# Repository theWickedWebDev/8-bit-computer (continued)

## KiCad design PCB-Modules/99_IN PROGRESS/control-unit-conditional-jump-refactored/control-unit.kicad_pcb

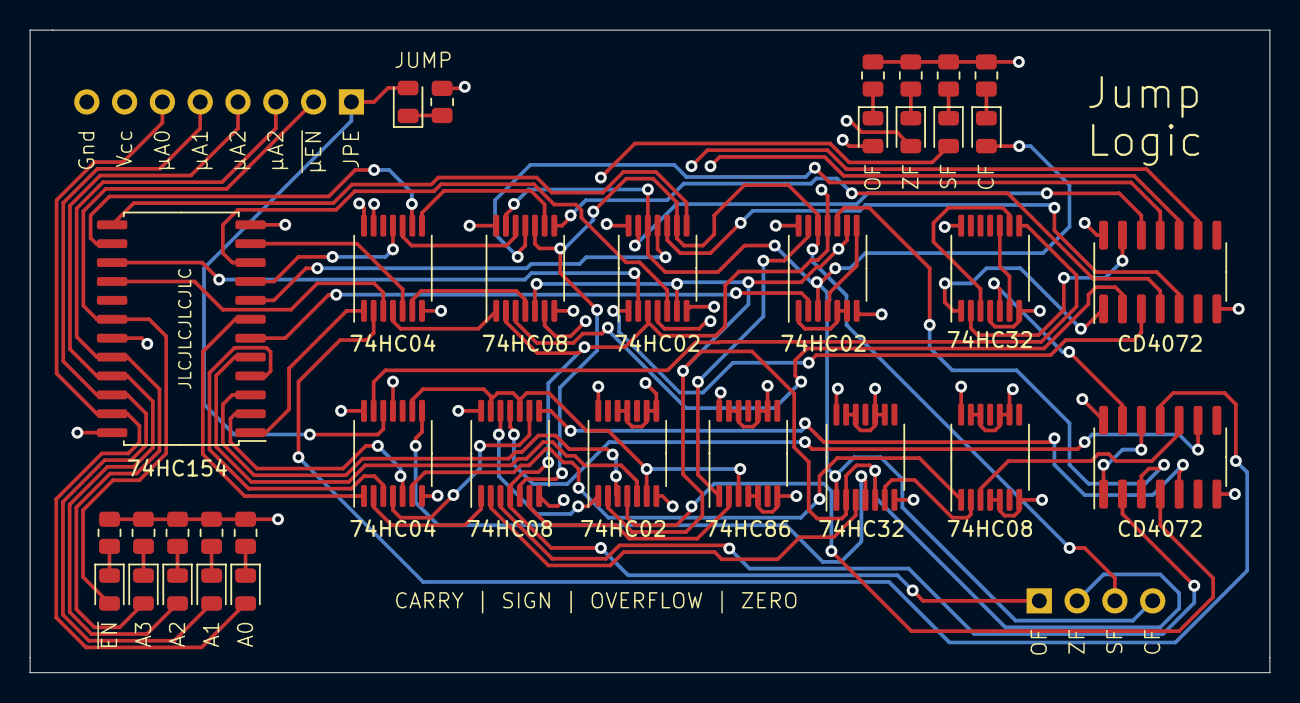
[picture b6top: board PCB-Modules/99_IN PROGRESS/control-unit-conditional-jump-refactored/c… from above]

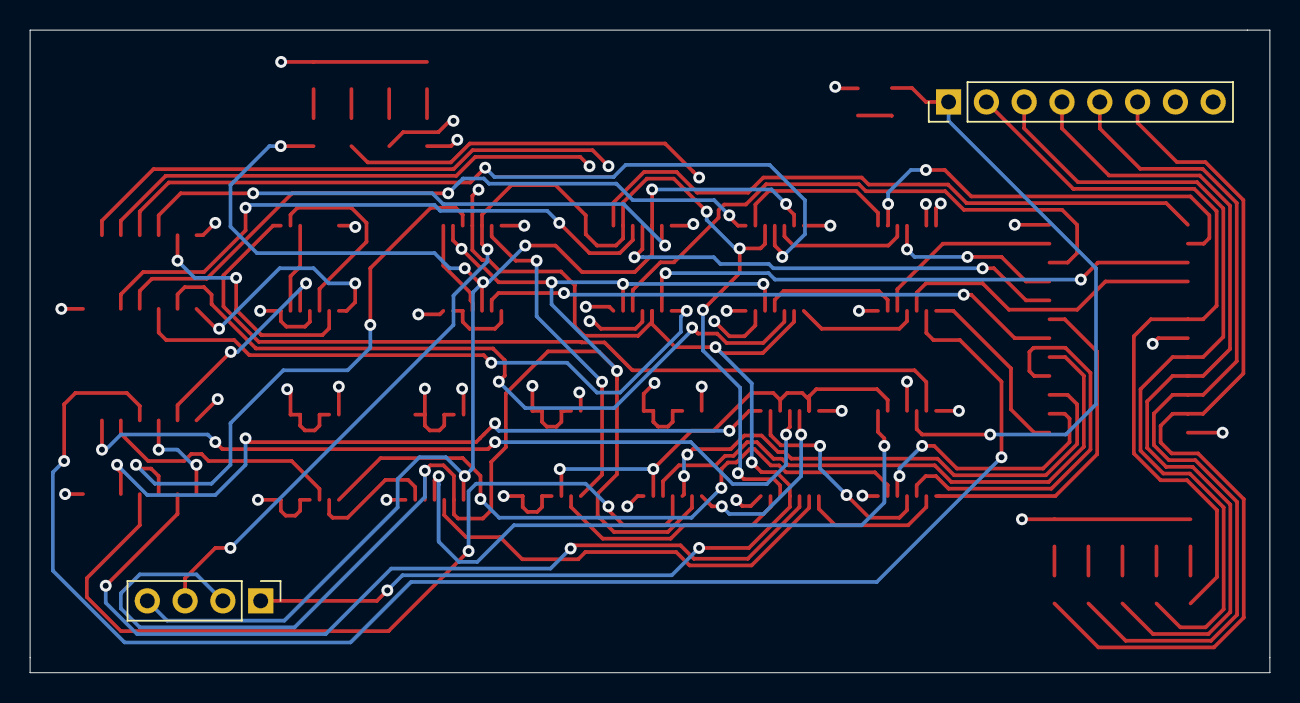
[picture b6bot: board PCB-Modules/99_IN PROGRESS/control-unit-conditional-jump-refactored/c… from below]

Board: 4 copper layers, 83.3 x 43.2 mm, 36 parts (2 on the bottom side), 75 nets.

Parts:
D1, D2, D3, D4, D5, D6, D7, D8, D9, D10: LED; LED_0805_2012Metric
J3: Conn_01x08; PinHeader_1x08_P2.54mm_Vertical
J4: Conn_01x04; PinHeader_1x04_P2.54mm_Vertical
R1, R2, R3, R4, R5, R6, R7, R8, R9, R10: R_US; R_0805_2012Metric
U1, U4: 74LS04; TSSOP-14_4.4x5mm_P0.65mm
U2, U5, U9: 74LS02; TSSOP-14_4.4x5mm_P0.65mm
U3, U6, U14: 74LS08; TSSOP-14_4.4x5mm_P0.65mm
U7, U12: 74LS32; TSSOP-14_4.4x5mm_P0.65mm
U8: 74LS86; TSSOP-14_4.4x5mm_P0.65mm
U10, U11: CD4072; SOIC-14_3.9x8.7mm_P1.27mm
U13: 74LS154; SOIC-24W_7.5x15.4mm_P1.27mm

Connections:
ADR0: D6.2, J3.6, U13.23
ADR1: D7.2, J3.5, U13.22
ADR2: D8.2, J3.4, U13.21
ADR3: D9.2, J3.3, U13.20
CARRY_FLAG: D2.2, J4.4, U2.12, U3.13, U5.3, U7.1
EN: D10.2, J3.2, U13.18
GND: J3.8, R1.2, R2.2, R3.2, R4.2, R5.2, R6.2, R7.2, R8.2, R9.2, R10.2, U1.7, U1.13, U2.7, U3.7, U4.7, U4.11, U5.7, U6.7, U7.7, U7.9, U7.10, U7.12, U7.13, U8.4, U8.5, U8.7, U8.9, U8.10, U8.12, U8.13, U9.7, U9.8, U9.9, U9.11, U9.12, U10.7, U11.7, U12.4, U12.7, U13.12, U13.19, U14.4, U14.5, U14.7, U14.9, U14.10, U14.12, U14.13
LOAD_PROGRAM_COUNTER_COND: D1.2, J3.1, U4.12
unnamed: D1.1, R1.1
unnamed: D2.1, R2.1
unnamed: D3.1, R3.1
unnamed: D4.1, R4.1
unnamed: D5.1, R5.1
unnamed: D6.1, R6.1
unnamed: D7.1, R7.1
unnamed: D8.1, R8.1
unnamed: D9.1, R9.1
unnamed: D10.1, R10.1
unnamed: U1.4, U3.1
unnamed: U1.6, U3.4
unnamed: U1.8, U3.9
unnamed: U1.10, U3.12
unnamed: U4.2, U6.1
unnamed: U4.4, U6.9
unnamed: U4.8, U7.4
unnamed: U5.1, U5.5, U5.6
unnamed: U5.4, U5.8
unnamed: U5.13, U8.1
unnamed: U6.2, U7.3
unnamed: U6.6, U8.2
unnamed: U6.12, U9.1
unnamed: U10.1, U12.1
unnamed: U10.13, U12.2
unnamed: U11.1, U11.12
unnamed: U11.13, U12.5
unnamed: U12.3, U12.9
unnamed: U4.13, U12.8
unnamed: U12.6, U12.10
unnamed: U4.6, U14.1
unnamed: U7.6, U14.2
OR_JA_JNBE: U5.10, U11.3
OR_JBE_JNA: U6.3, U11.2
OR_JB_JNAE_JC: U3.11, U10.11
OR_JE_JZ: U3.6, U10.9
OR_JGE_JNL: U6.8, U11.5
OR_JG_JNLE: U6.11, U11.9
OR_JLE_JNG: U11.10, U14.3
OR_JL_JNGE: U9.4, U11.4
OR_JNB_JAE_JNC: U2.13, U10.12
OR_JNE_JNZ: U2.4, U10.10
OR_JNO: U2.1, U10.3
OR_JNS: U2.10, U10.5
OR_JO: U3.3, U10.2
OR_JS: U3.8, U10.4
OR_JUMP: U1.2, U11.11
OVERFLOW_FLAG: D5.2, J4.1, U2.3, U3.2, U5.11, U6.4
SF=OF: U4.9, U6.10, U6.13, U8.3, U9.6
SIGN_FLAG: D3.2, J4.3, U2.9, U3.10, U5.12, U6.5
VCC: J3.7, U1.14, U2.14, U3.14, U4.14, U5.14, U6.14, U7.14, U8.14, U9.14, U10.14, U11.14, U12.14, U13.24, U14.14
ZERO_FLAG: D4.2, J4.2, U2.6, U3.5, U5.9, U7.2, U7.5, U9.2
~J: U1.1, U13.1
~JA_JNBE: U5.2, U13.6
~JBE_JNA: U4.1, U13.7
~JB_JNAE_JC: U1.11, U13.9
~JE_JZ: U1.5, U13.11
~JGE_JNL: U4.3, U13.4
~JG_JNLE: U9.3, U13.3
~JLE_JNG: U4.5, U13.2
~JL_JNGE: U9.5, U13.5
~JNB_JAE_JNC: U2.11, U13.8
~JNE_JNZ: U2.5, U13.10
~JNO: U2.2, U13.15
~JNS: U2.8, U13.13
~JO: U1.3, U13.16
~JS: U1.9, U13.14

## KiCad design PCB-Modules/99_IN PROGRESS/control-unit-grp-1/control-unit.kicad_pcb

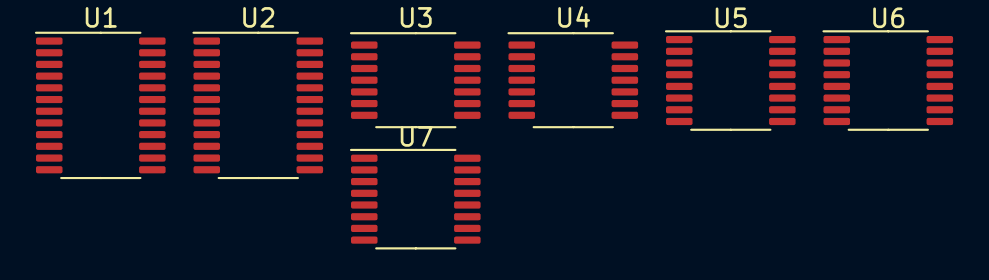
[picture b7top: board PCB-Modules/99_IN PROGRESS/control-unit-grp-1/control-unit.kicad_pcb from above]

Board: 4 copper layers, 7 parts (0 on the bottom side), 18 nets, no tracks yet.

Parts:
U1, U2: 74LS154; TSSOP-24_4.4x7.8mm_P0.65mm
U3: 74LS08; TSSOP-14_4.4x5mm_P0.65mm
U4: 74HC04; TSSOP-14_4.4x5mm_P0.65mm
U5: 74LS157; TSSOP-16_4.4x5mm_P0.65mm
U6, U7: 74LS258; TSSOP-16_4.4x5mm_P0.65mm

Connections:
EEPROM_0: U1.23, U2.23, U5.2
EEPROM_1: U1.22, U2.22, U5.5
EEPROM_2: U1.21, U2.21, U5.11
EEPROM_3: U1.20, U2.20, U5.14
GND: U1.12, U2.12, U3.7, U4.7, U5.3, U5.6, U5.8, U5.10, U5.13, U5.15, U6.2, U6.6, U6.8, U6.10, U6.11, U6.13, U6.14, U7.3, U7.6, U7.8, U7.10, U7.11, U7.13, U7.14
unnamed: U3.3, U6.15
unnamed: U3.5, U3.8
unnamed: U3.6, U5.1
unnamed: U3.13, U4.2
SHA_SEL_00: U6.7, U7.7
SHA_SEL_01: U6.4, U7.4
VCC: U1.24, U2.24, U3.14, U4.14, U5.16, U6.3, U6.5, U6.16, U7.2, U7.5, U7.16
~ALU_MODE_0_CARRY_IN_EN: U3.4, U4.1
~LOAD_A_REGISTER: U2.7, U7.1, U7.15
~SHIFT_A_LEFT: U2.8, U3.2
~SHIFT_A_RIGHT: U2.9, U3.1, U6.1
~WRITE_MUX0_EN: U1.18, U1.19
~WRITE_MUX1_EN: U2.18, U2.19

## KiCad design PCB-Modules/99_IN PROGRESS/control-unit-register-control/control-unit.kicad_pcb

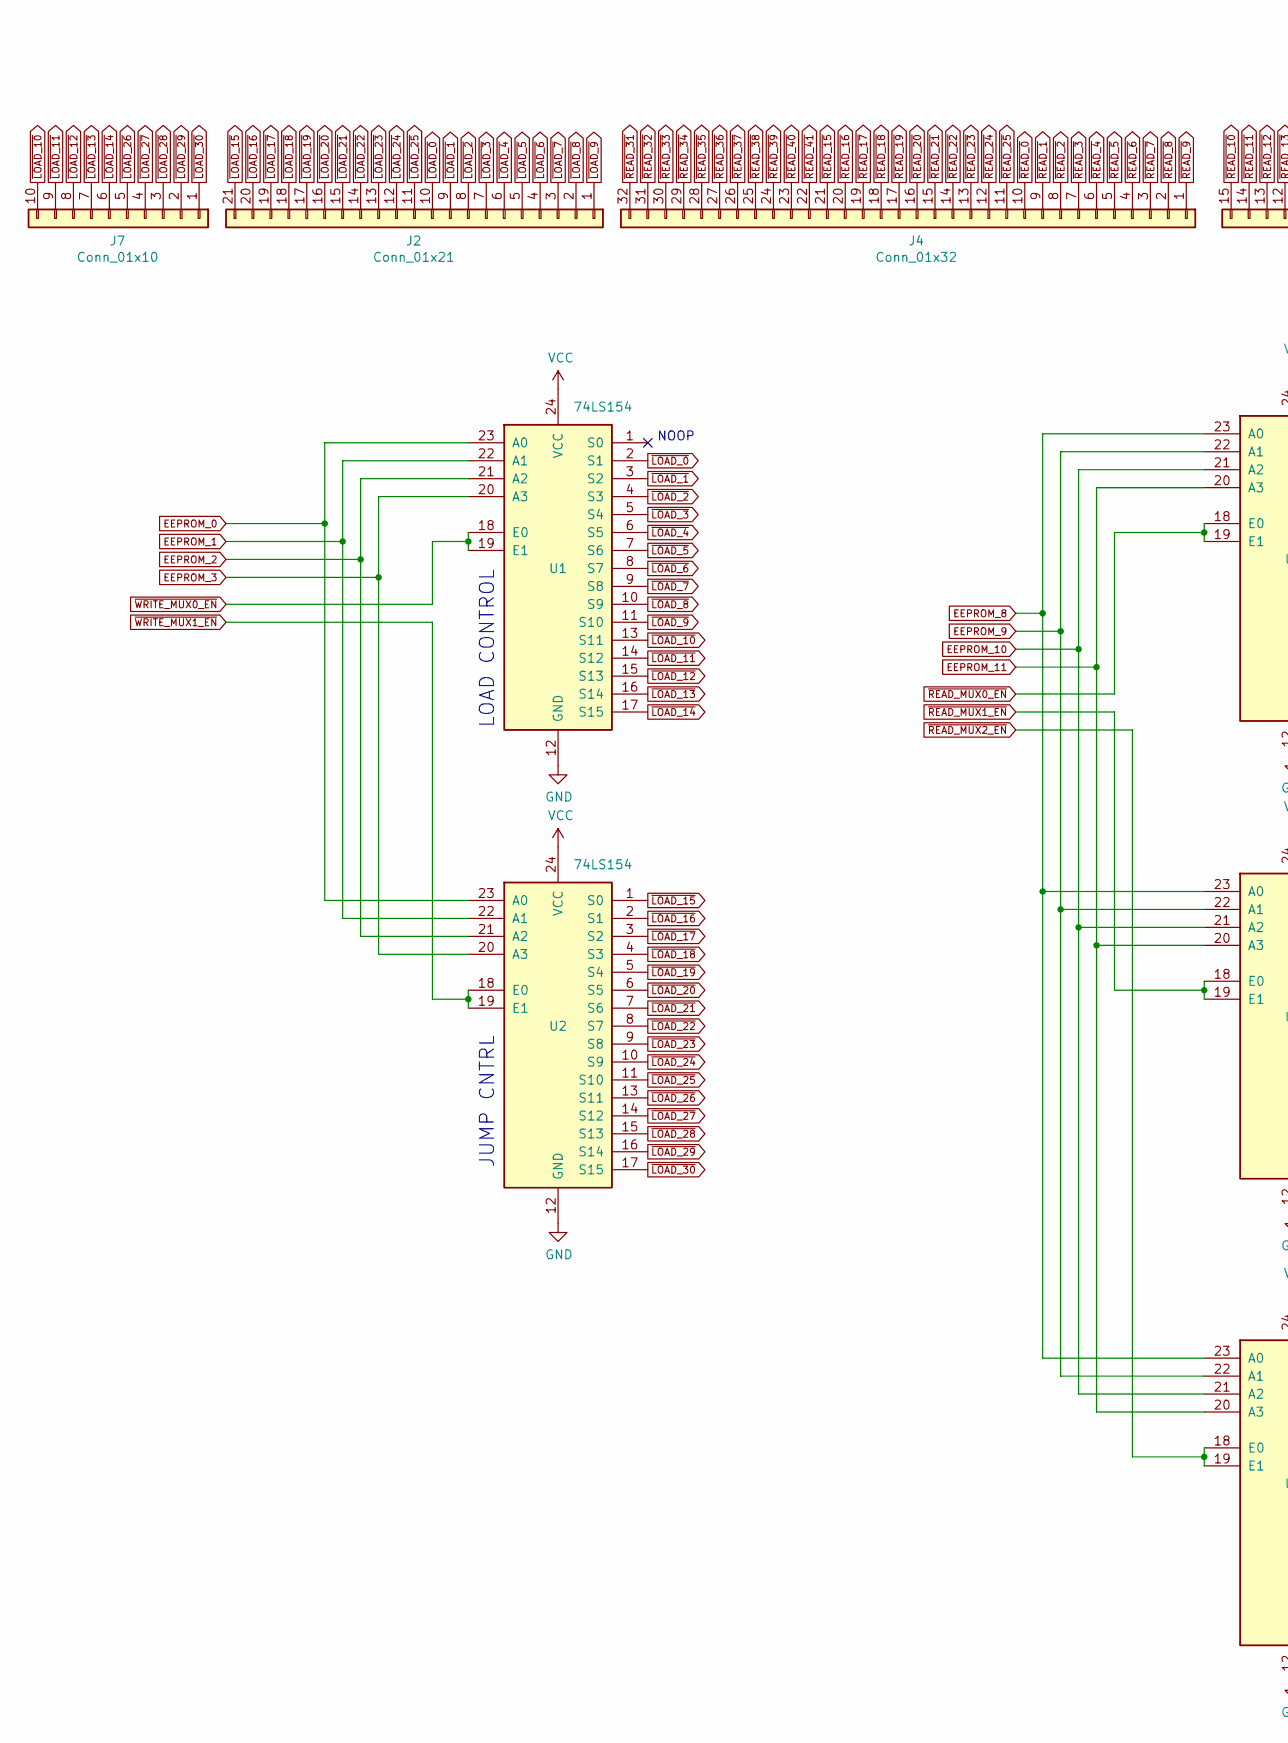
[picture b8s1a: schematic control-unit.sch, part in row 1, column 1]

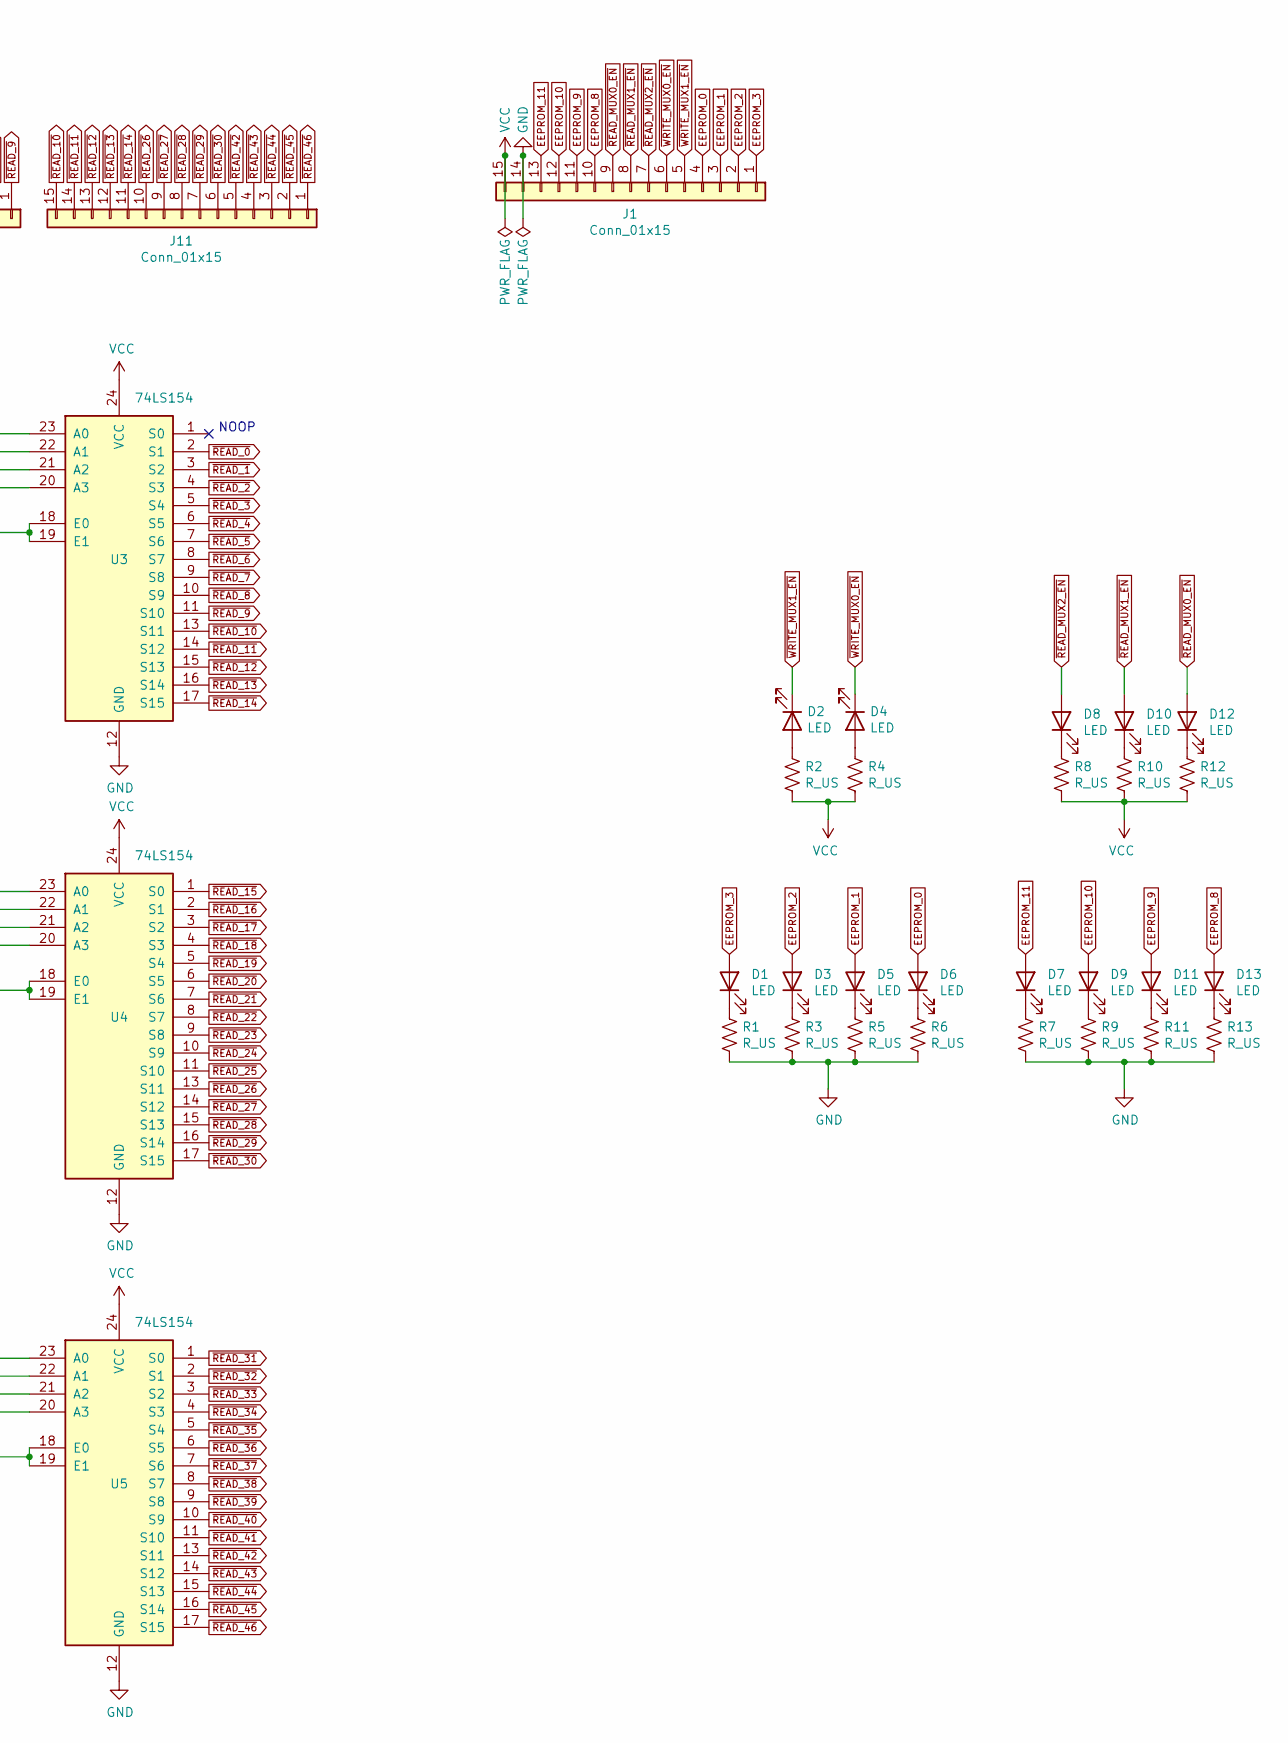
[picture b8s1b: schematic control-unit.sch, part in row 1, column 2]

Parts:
D1, D2, D3, D4, D5, D6, D7, D8, D9, D10, D11, D12, D13: LED; LED_0805_2012Metric
J1, J11: Conn_01x15; PinHeader_1x15_P2.54mm_Vertical
J2: Conn_01x21; PinHeader_1x21_P2.54mm_Vertical
J4: Conn_01x32; PinHeader_1x32_P2.54mm_Vertical
J7: Conn_01x10; PinHeader_1x10_P2.54mm_Vertical
R1, R2, R3, R4, R5, R6, R7, R8, R9, R10, R11, R12, R13: R_US; R_0805_2012Metric
U1, U2, U3, U4, U5: 74LS154; TSSOP-24_4.4x7.8mm_P0.65mm

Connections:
EEPROM_0: D6.2 (A), J1.4, U1.23 (A0), U2.23 (A0)
EEPROM_1: D5.2 (A), J1.3, U1.22 (A1), U2.22 (A1)
EEPROM_2: D3.2 (A), J1.2, U1.21 (A2), U2.21 (A2)
EEPROM_3: D1.2 (A), J1.1, U1.20 (A3), U2.20 (A3)
EEPROM_8: D13.2 (A), J1.10, U3.23 (A0), U4.23 (A0), U5.23 (A0)
EEPROM_9: D11.2 (A), J1.11, U3.22 (A1), U4.22 (A1), U5.22 (A1)
EEPROM_10: D9.2 (A), J1.12, U3.21 (A2), U4.21 (A2), U5.21 (A2)
EEPROM_11: D7.2 (A), J1.13, U3.20 (A3), U4.20 (A3), U5.20 (A3)
GND: J1.14, R1.2, R3.2, R5.2, R6.2, R7.2, R9.2, R11.2, R13.2, U1.12 (GND), U2.12 (GND), U3.12 (GND), U4.12 (GND), U5.12 (GND)
unnamed: D1.1 (K), R1.1
unnamed: D2.2 (A), R2.1
unnamed: D3.1 (K), R3.1
unnamed: D4.2 (A), R4.1
unnamed: D5.1 (K), R5.1
unnamed: D6.1 (K), R6.1
unnamed: D7.1 (K), R7.1
unnamed: D8.1 (K), R8.1
unnamed: D9.1 (K), R9.1
unnamed: D10.1 (K), R10.1
unnamed: D11.1 (K), R11.1
unnamed: D12.1 (K), R12.1
unnamed: D13.1 (K), R13.1
VCC: J1.15, R2.2, R4.2, R8.2, R10.2, R12.2, U1.24 (VCC), U2.24 (VCC), U3.24 (VCC), U4.24 (VCC), U5.24 (VCC)
~LOAD_0: J2.10, U1.2 (S1)
~LOAD_1: J2.9, U1.3 (S2)
~LOAD_2: J2.8, U1.4 (S3)
~LOAD_3: J2.7, U1.5 (S4)
~LOAD_4: J2.6, U1.6 (S5)
~LOAD_5: J2.5, U1.7 (S6)
~LOAD_6: J2.4, U1.8 (S7)
~LOAD_7: J2.3, U1.9 (S8)
~LOAD_8: J2.2, U1.10 (S9)
~LOAD_9: J2.1, U1.11 (S10)
~LOAD_10: J7.10, U1.13 (S11)
~LOAD_11: J7.9, U1.14 (S12)
~LOAD_12: J7.8, U1.15 (S13)
~LOAD_13: J7.7, U1.16 (S14)
~LOAD_14: J7.6, U1.17 (S15)
~LOAD_15: J2.21, U2.1 (S0)
~LOAD_16: J2.20, U2.2 (S1)
~LOAD_17: J2.19, U2.3 (S2)
~LOAD_18: J2.18, U2.4 (S3)
~LOAD_19: J2.17, U2.5 (S4)
~LOAD_20: J2.16, U2.6 (S5)
~LOAD_21: J2.15, U2.7 (S6)
~LOAD_22: J2.14, U2.8 (S7)
~LOAD_23: J2.13, U2.9 (S8)
~LOAD_24: J2.12, U2.10 (S9)
~LOAD_25: J2.11, U2.11 (S10)
~LOAD_26: J7.5, U2.13 (S11)
~LOAD_27: J7.4, U2.14 (S12)
~LOAD_28: J7.3, U2.15 (S13)
~LOAD_29: J7.2, U2.16 (S14)
~LOAD_30: J7.1, U2.17 (S15)
~READ_0: J4.10, U3.2 (S1)
~READ_1: J4.9, U3.3 (S2)
~READ_2: J4.8, U3.4 (S3)
~READ_3: J4.7, U3.5 (S4)
~READ_4: J4.6, U3.6 (S5)
~READ_5: J4.5, U3.7 (S6)
~READ_6: J4.4, U3.8 (S7)
~READ_7: J4.3, U3.9 (S8)
~READ_8: J4.2, U3.10 (S9)
~READ_9: J4.1, U3.11 (S10)
~READ_10: J11.15, U3.13 (S11)
~READ_11: J11.14, U3.14 (S12)
~READ_12: J11.13, U3.15 (S13)
~READ_13: J11.12, U3.16 (S14)
~READ_14: J11.11, U3.17 (S15)
~READ_15: J4.21, U4.1 (S0)
~READ_16: J4.20, U4.2 (S1)
~READ_17: J4.19, U4.3 (S2)
~READ_18: J4.18, U4.4 (S3)
~READ_19: J4.17, U4.5 (S4)
~READ_20: J4.16, U4.6 (S5)
~READ_21: J4.15, U4.7 (S6)
~READ_22: J4.14, U4.8 (S7)
~READ_23: J4.13, U4.9 (S8)
~READ_24: J4.12, U4.10 (S9)
~READ_25: J4.11, U4.11 (S10)
~READ_26: J11.10, U4.13 (S11)
~READ_27: J11.9, U4.14 (S12)
~READ_28: J11.8, U4.15 (S13)
~READ_29: J11.7, U4.16 (S14)
~READ_30: J11.6, U4.17 (S15)
~READ_31: J4.32, U5.1 (S0)
~READ_32: J4.31, U5.2 (S1)
~READ_33: J4.30, U5.3 (S2)
~READ_34: J4.29, U5.4 (S3)
~READ_35: J4.28, U5.5 (S4)
~READ_36: J4.27, U5.6 (S5)
~READ_37: J4.26, U5.7 (S6)
~READ_38: J4.25, U5.8 (S7)
~READ_39: J4.24, U5.9 (S8)
~READ_40: J4.23, U5.10 (S9)
~READ_41: J4.22, U5.11 (S10)
~READ_42: J11.5, U5.13 (S11)
~READ_43: J11.4, U5.14 (S12)
~READ_44: J11.3, U5.15 (S13)
~READ_45: J11.2, U5.16 (S14)
~READ_46: J11.1, U5.17 (S15)
~READ_MUX0_EN: D12.2 (A), J1.9, U3.18 (E0), U3.19 (E1)
~READ_MUX1_EN: D10.2 (A), J1.8, U4.18 (E0), U4.19 (E1)
~READ_MUX2_EN: D8.2 (A), J1.7, U5.18 (E0), U5.19 (E1)
~WRITE_MUX0_EN: D4.1 (K), J1.6, U1.18 (E0), U1.19 (E1)
~WRITE_MUX1_EN: D2.1 (K), J1.5, U2.18 (E0), U2.19 (E1)

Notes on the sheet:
NOOP
JUMP CNTRL
LOAD CONTROL

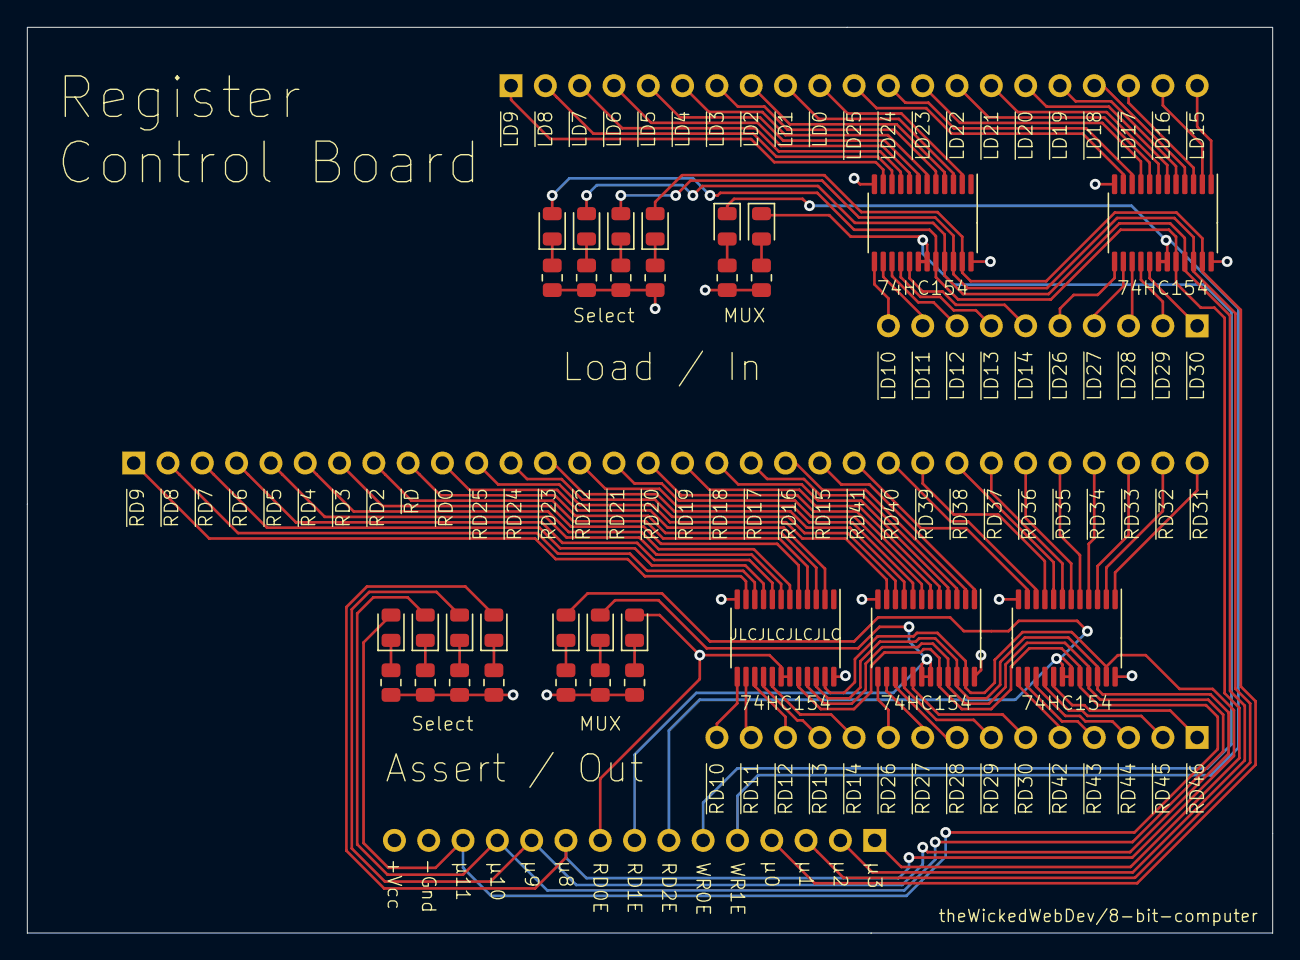
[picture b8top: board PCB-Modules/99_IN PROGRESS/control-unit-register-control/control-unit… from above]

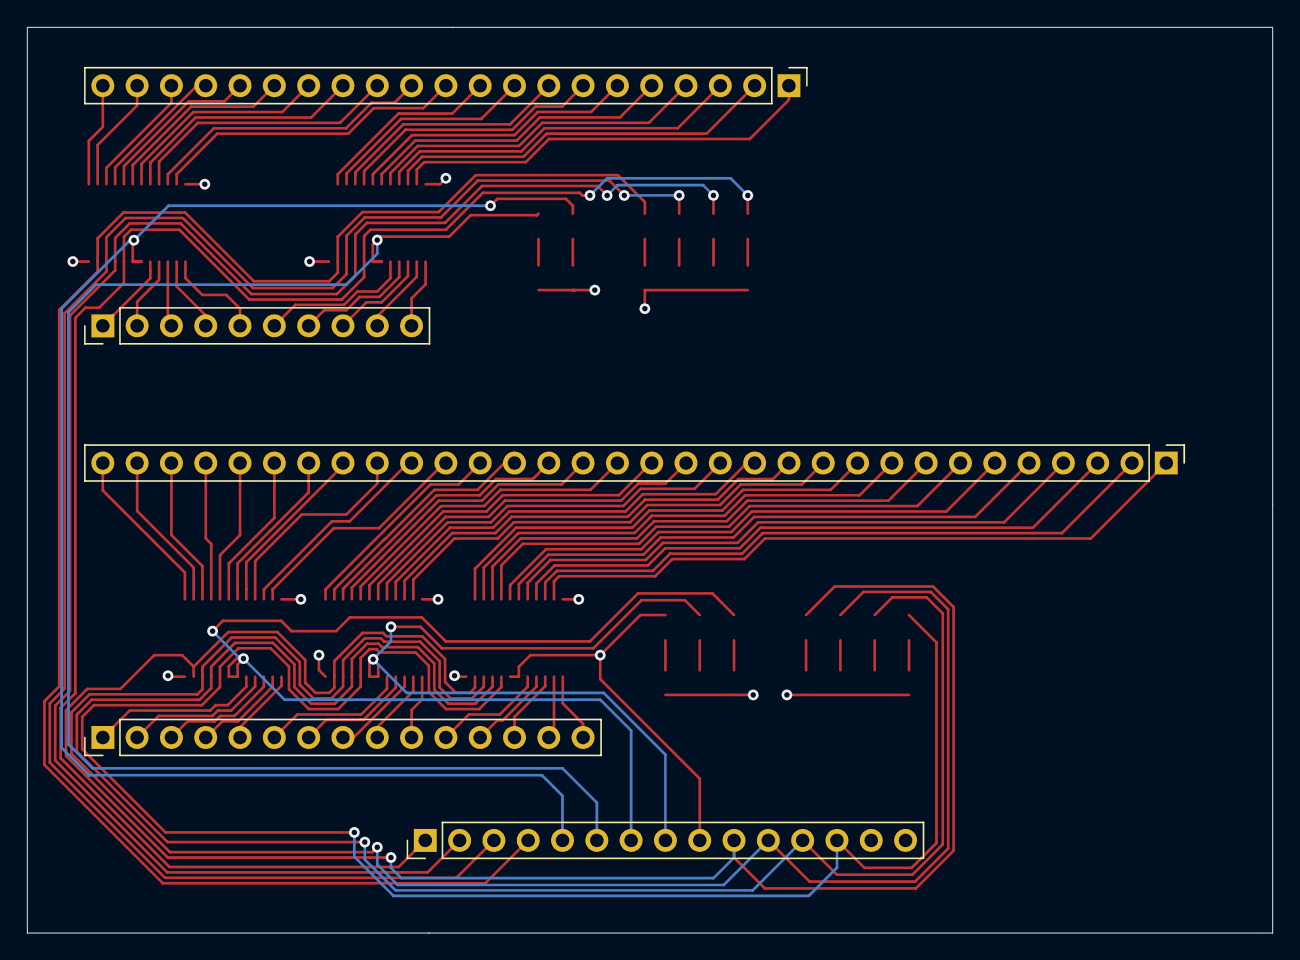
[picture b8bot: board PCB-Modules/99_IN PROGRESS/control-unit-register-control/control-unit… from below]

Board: 4 copper layers, 92.2 x 67.1 mm, 36 parts (5 on the bottom side), 106 nets.
